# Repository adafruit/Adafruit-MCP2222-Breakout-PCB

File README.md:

## Adafruit MCP2222 Breakout - General Purpose USB to GPIO/SPI/I2C - Stemma QT / Qwiic PCB

<a href="http://www.adafruit.com/products/6559"><br/>
Click here to purchase one from the Adafruit shop</a>

PCB files for the Adafruit MCP2222 Breakout - General Purpose USB to GPIO/SPI/I2C - Stemma QT / Qwiic. 

Format is EagleCAD schematic and board layout
* https://www.adafruit.com/product/6559

### Description

Wouldn't it be cool to drive a [tiny OLED display](https://www.adafruit.com/categories/98), read a [color sensor](https://www.adafruit.com/product/6461), or even just flash some LEDs directly from your computer?  Sure you can program an [Arduino](https://www.adafruit.com/products/50) or [QT Py](https://www.adafruit.com/search?q=qt+py) to talk to these devices and your computer, but why can't your computer just talk to those devices and sensors itself?  Well, now your computer *can* talk to devices using the Adafruit MCP2222 breakout board\!

What can the MCP2222 chip do?  This chip from [Microchip](https://www.microchip.com/en-us/product/mcp2222) is similar to a USB to serial converter chips but adds a GPIO, UART Serial, SPI and I2C interface as well. The I2C interface is great for talking to OLEDs, sensors, PWM drivers, its the most popular interface for small devices. SPI is for more sensors and many TFT displays. You can use the GPIO to do things like flash LEDs, read switches or buttons, and more. The MCP2222 breakout is like adding a little multi-tool for serial protocols to your computer\!

One nifty capability of the MCP2222, unlike most USB-to-GPIO converters is the ability to use 3.3V *or* 5V logic. This makes it good for interfacing with some older sensors and devices that want 5V signals.

Please note: The MCP2222 has more GPIO than the MCP2221, and comes with SPI too. But it does not have ADC or DAC like the '2221. Also, the SPI has inter-byte gaps so it cannot be used for 'fake' NeoPixel writes by modulating the MOSI pin.

This chip is powerful and useful to have when you want to use Python (for example) to quickly iterate and test a device that uses SPI, UART, I2C or general purpose digital  I/O. There's no firmware to deal with, so you don't have to deal with how to "send data to and from an Arduino which is then sent to and from" an electronic sensor or display or part.

This breakout has an MCP2222 chip, USB C connector, on-board 3V regulator, and a 4 pin JST SH port for I2C connectivity with 3V or 5V power and logic. [This port is Stemma QT / Qwiic compatible](https://adafruit.com/stemma) for use with any sensor or chip that that has a matching port \- you can even wire in Grove I2C devices with an adapter cable with no soldering required\! [See this guide for more info on Stemma QT](https://learn.adafruit.com/introducing-adafruit-stemma-qt)

[Check out all our Stemma QT sensors, cables, and devices you can use here.](http://adafruit.com/stemma)

### License

Adafruit invests time and resources providing this open source design, please support Adafruit and open-source hardware by purchasing products from [Adafruit](https://www.adafruit.com)!

Designed by Limor Fried/Ladyada for Adafruit Industries.

Creative Commons Attribution/Share-Alike, all text above must be included in any redistribution. 
See license.txt for additional details.

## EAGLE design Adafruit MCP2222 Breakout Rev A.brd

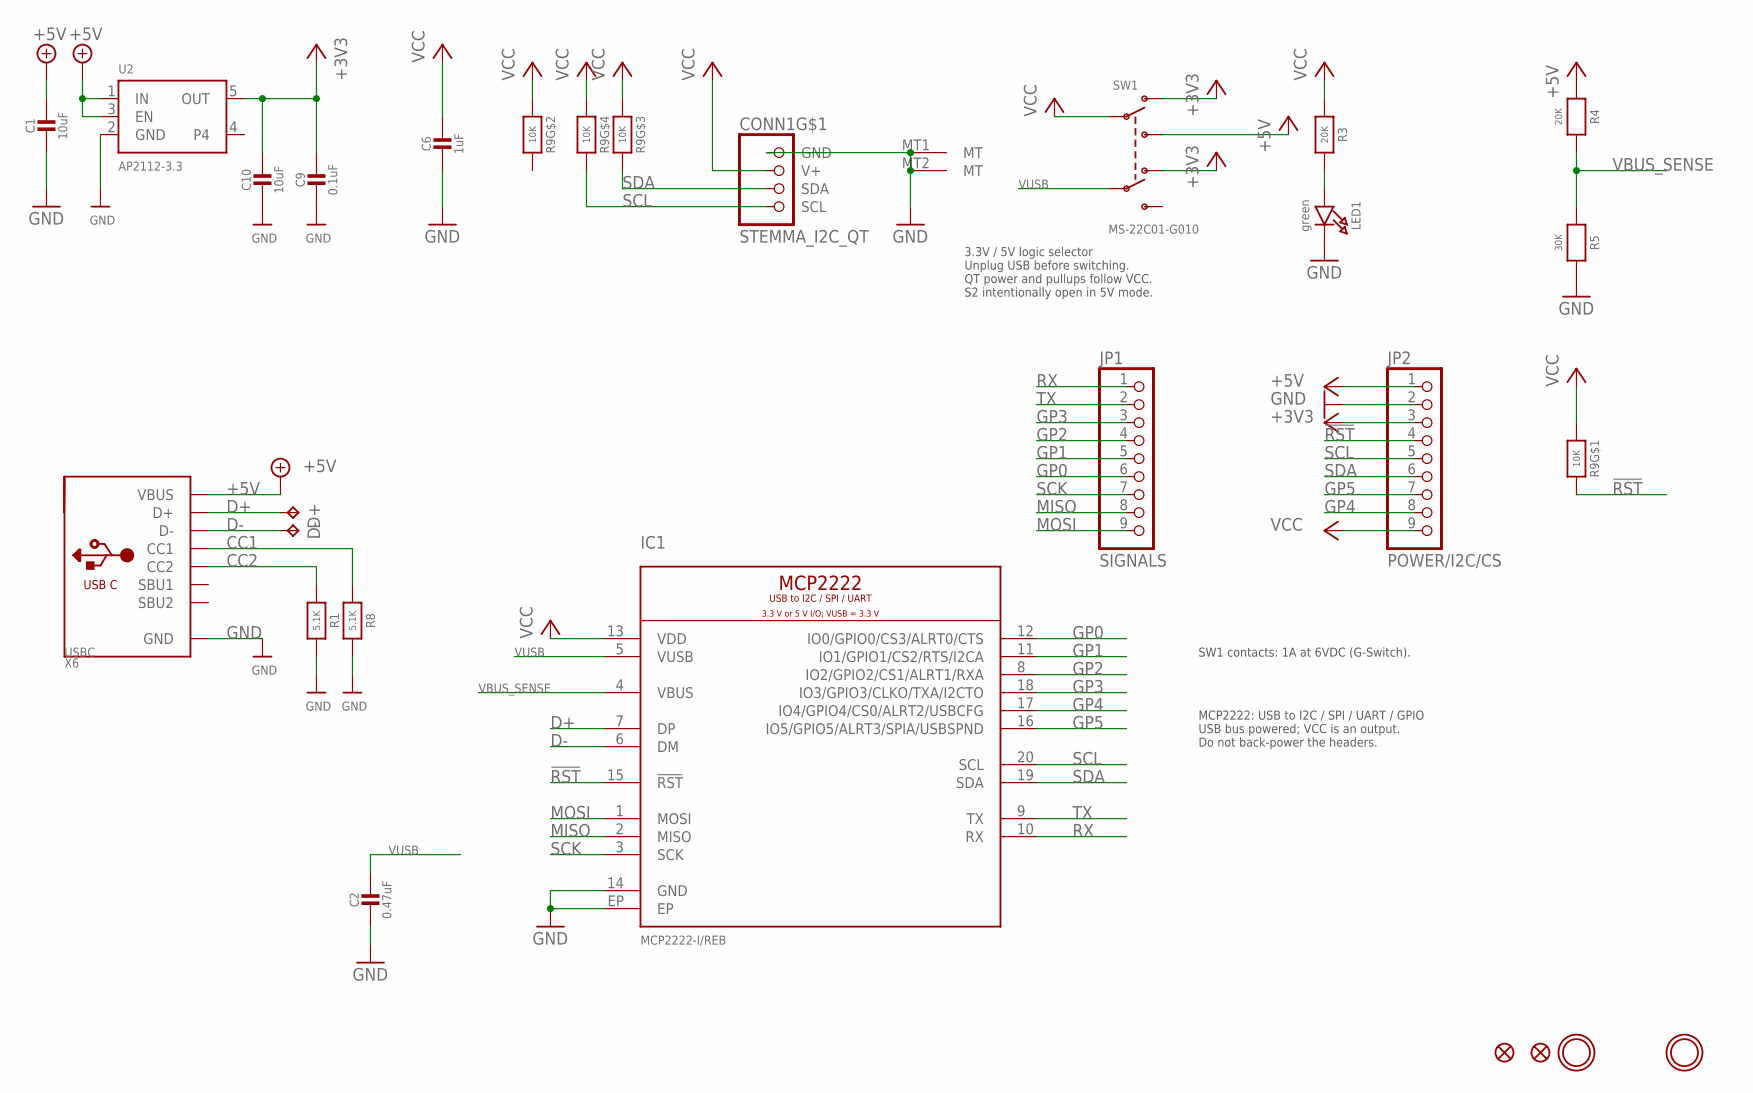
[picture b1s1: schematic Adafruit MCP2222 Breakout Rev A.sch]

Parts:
C1, C10: 10uF; 0805-NO
C2: 0.47uF; 0603-NO
C6: 1uF; 0603-NO
C9: 0.1uF; 0603-NO
CONN1: STEMMA_I2C_QT; JST_SH4
D+: TPTP17R; TP17R
D-: TPTP17R; TP17R
FID1, FID2: FIDUCIAL_0.5MM
IC1: MCP2222-I/REB; VQFN20_3X3_P04_EP18_MCP2222
JP1: SIGNALS; 1X09_ROUND_70
JP2: POWER/I2C/CS; 1X09_ROUND_70
LED1: green; CHIPLED_0603_NOOUTLINE
R1, R8: 5.1K; 0603-NO
R3, R4: 20K; 0603-NO
R5: 30K; 0603-NO
R9: 10K; RESPACK_4X0603
SW1: MS-22C01-G010; EG1390; MPN MS-22C01-G010
U2: AP2112-3.3; SOT23-5; JLC_ROTATION 0
U$6, U$7: MOUNTINGHOLE2.5; MOUNTINGHOLE_2.5_PLATED
X6: USBC; USB_C_CUSB31-CFM2AX-01-X

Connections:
!RST: IC1.15 (!RST), JP2.4, R9.8 (2)
+3V3: C9.1, C10.1, JP2.3, SW1.O1, SW1.O2, U2.5 (OUT)
+5V: C1.1, JP2.1, R4.1, SW1.S1, U2.1 (IN), U2.3 (EN), X6.A4B9 (VBUS), X6.B4A9 (VBUS)
CC1: R8.1, X6.A5 (CC1)
CC2: R1.1, X6.B5 (CC2)
D+: D+.TP, IC1.7 (DP), X6.A6 (D+), X6.B6 (D+)
D-: D-.TP, IC1.6 (DM), X6.A7 (D-), X6.B7 (D-)
GND: C1.2, C2.2, C6.2, C9.2, C10.2, CONN1.1 (GND), CONN1.MT1 (MT), CONN1.MT2 (MT), IC1.14 (GND), IC1.EP, JP2.2, LED1.C, R1.2, R5.2, R8.2, U2.2 (GND), X6.A1B12 (GND), X6.B1A12 (GND)
GP0: IC1.12 (IO0/GPIO0/CS3/ALRT0/CTS), JP1.6
GP1: IC1.11 (IO1/GPIO1/CS2/RTS/I2CA), JP1.5
GP2: IC1.8 (IO2/GPIO2/CS1/ALRT1/RXA), JP1.4
GP3: IC1.18 (IO3/GPIO3/CLKO/TXA/I2CTO), JP1.3
GP4: IC1.17 (IO4/GPIO4/CS0/ALRT2/USBCFG), JP2.8
GP5: IC1.16 (IO5/GPIO5/ALRT3/SPIA/USBSPND), JP2.7
MISO: IC1.2 (MISO), JP1.8
MOSI: IC1.1 (MOSI), JP1.9
unnamed: LED1.A, R3.2
RX: IC1.10 (RX), JP1.1
SCK: IC1.3 (SCK), JP1.7
SCL: CONN1.4 (SCL), IC1.20 (SCL), JP2.5, R9.5 (2)
SDA: CONN1.3 (SDA), IC1.19 (SDA), JP2.6, R9.6 (2)
TX: IC1.9 (TX), JP1.2
VBUS_SENSE: IC1.4 (VBUS), R4.2, R5.1
VCC: C6.1, CONN1.2 (V+), IC1.13 (VDD), JP2.9, R3.1, R9.1, R9.2 (1), R9.3 (1), R9.4 (1), SW1.P1
VUSB: C2.1, IC1.5 (VUSB), SW1.P2

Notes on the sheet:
3.3V / 5V logic selector Unplug USB before switching. QT power and pullups follow VCC. S2 intentionally open in 5V mode.
MCP2222: USB to I2C / SPI / UART / GPIO USB bus powered; VCC is an output. Do not back-power the headers.
SW1 contacts: 1A at 6VDC (G-Switch).

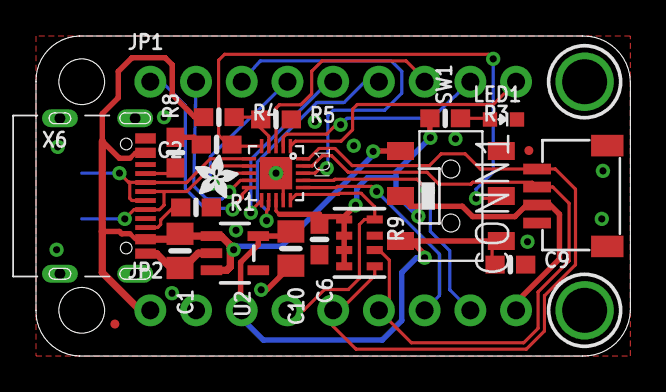
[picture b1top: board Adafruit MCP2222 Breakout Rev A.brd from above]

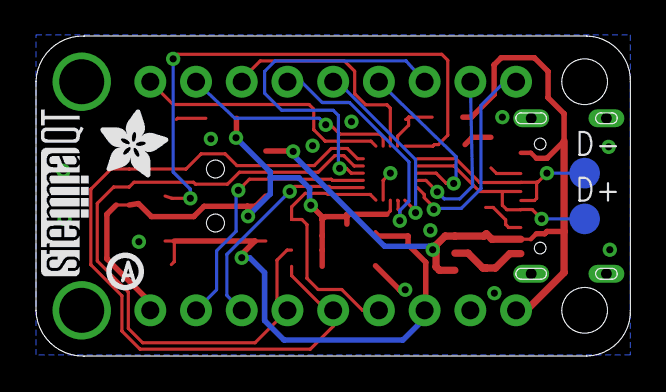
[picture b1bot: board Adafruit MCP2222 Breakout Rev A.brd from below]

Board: 2 copper layers, 33.0 x 17.8 mm, 55 parts (7 on the bottom side), 25 nets.

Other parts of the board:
PLABEL0: PLABEL0
PLABEL1: PLABEL1
PLABEL2: PLABEL2
PLABEL3: PLABEL3
PLABEL4: PLABEL4
PLABEL5: PLABEL5
PLABEL6: PLABEL6
PLABEL7: PLABEL7
PLABEL8: PLABEL8
PLABEL9: PLABEL9
PLABEL10: PLABEL10
PLABEL11: PLABEL11
PLABEL12: PLABEL12
PLABEL13: PLABEL13
PLABEL14: PLABEL14
PLABEL15: PLABEL15
PLABEL16: PLABEL16
PLABEL17: PLABEL17
PLABEL18: PLABEL18
PLABEL19: PLABEL19
PLABEL20: PLABEL20
PLABEL21: PLABEL21
PLABEL22: PLABEL22
PLABEL23: PLABEL23
PLABEL24: PLABEL24
PLABEL25: PLABEL25
U$1: ADAFRUIT_3.5MM
U$2: ADAFRUIT_2.5MM
U$3: STEMMAQT
U$4: PCBFEAT-REV-040

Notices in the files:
parts and their libraries:
microbuilder: This work is placed in the public domain, and may be freely used for commercial and non-commercial work with the following conditions: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
